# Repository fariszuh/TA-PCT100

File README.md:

# Tugas  Akhir PCT-100
Repository ini berisi file tugas akhir Implementasi PCT-100.
File yang tersedia berisi file program TA yang dibuat Penulis Muhammad Faris Zuhairi (2019 / Wisudawan 128 ITS), 
dengan judul berikut:

PERANCANGAN KONTROLER TERTANAM MENGGUNAKAN DIRECT NEURAL NETWORK UNTUK PENGATURAN LEVEL TANGKI PCT-100

Link Tugas Akhir: https://repository.its.ac.id/98936/ 
atau pada direktori "**Faris's Undergraduate Thesis (Buku TA)/07111940000164-Undergraduate_Thesis.pdf**"

Berikut foto prototype yang dibuat dan dihibahkan ke Lab. Kontrol dan Otomasi Dept. Teknik Elektro ITS

## 1. Tahap Permodelan
Tahap ini model plant diambil menggunakan identifikasi plant dan penurunan rumus. 
Permodelan dimulai dengan mengambil data menggunakan STM32 dengan hasil datasets terdapat pada folder berikut:
+ **/Datasets for Modelling & Test Result/**
  - **/Karakteristik Drain Valve/** :
  Data yang digunakan untuk memodelkan drain valve.

    Divariasikan: tegangan drain (Vdrain) dan tegangan flow control valve (Vfc).
    Dijaga konstan: tegangan pompa (Vpompa) 10V.

  - **/Karakteristik Flow Control Valve/** :
  Data yang digunakan untuk memodelkan flow control valve.

    Divariasikan: tegangan pompa (Vpompa) dan tegangan flow control valve (Vfc).
    Dijaga konstan: tegangan drain (Vdrain) tertutup (0 VDC).

  - **/Karakteristik Pompa/** :
  Data yang digunakan untuk memodelkan pompa inlet.

    Divariasikan: tegangan pompa (Vpompa).
    Dijaga konstan: tegangan drain (Vdrain) tertutup (0 VDC) dan dan tegangan flow control valve (22 VDC).

  - **/Karakteristik AI USB4716/** :
    Hasil pengujian DAC Amplifier AO STM32 dengan AI USB4716.
    Pengambilan data ini tanpa menghubungkan prototype ke plant (actuator dan sensor).
    Kode pengujian ini ada di folder **/Pengujian (Testing)/**.
  
    Divariasikan: tegangan AO STM32.

  - **/Karakteristik AO USB4716/** :
    Hasil pengujian ADC AI STM32 dengan AO USB4716.
    Pengambilan data ini tanpa menghubungkan prototype ke plant (actuator dan sensor).
    Kode pengujian ini ada di folder **/Pengujian (Testing)/**.

    Divariasikan: tegangan AO USB4716.

  - **/Pengujian NN/Implementasi/** :
    Hasil pengujian algoritma NN yang ditanam pada STM32.
    Pengambilan data ini dengan menghubungkan prototype ke plant (actuator dan sensor).
  
    Divariasikan: learning rate konstan dan nilai alpha (adaptasi learning rate) --> sudah dipisahkan dalam 2 folder yang berbeda.

  - **/Rafif Firdiansyah's Level Sensor Data/** :
    Excel workbook pembacaan tegangan level sensor dan simpangannya dengan level aktual (cm).

  - **/With Both Drain Valve/** :
    Data yang digunakan untuk memodelkan kedua valve pada kondisi berikut:
    Terbuka: manual dan motor drain valve.
    Tertutup: tidak ada.

      Divariasi: tegangan drain (Vdrain).
    
      Dijaga konstan: tegangan pompa (10 Vpompa) dan tegangan flow control valve (15 Vfc).
  
  - **/with Manual Valve/** :
    Data yang digunakan untuk memodelkan manual valve pada kondisi berikut:
    Terbuka: manual drain valve.
    Tertutup: motor drain valve --> tegangan drain (0 Vdrain) .

      Divariasi: tegangan pompa (Vpompa), dan tegangan flow control valve (Vfc).
    
      Dijaga konstan: full open manual valve.

  - **/with Proportional Drain Valve/** :
    Data yang digunakan untuk memodelkan motor valve pada kondisi berikut:
    Terbuka: motor drain valve.
    Tertutup: manual drain valve.

      Divariasi: tegangan flow control valve (15 Vfc).
    
      Dijaga konstan: tegangan drain (Vdrain) dan tegangan pompa (Vpompa).

Sedangkan, folder berikut berisi file program DAQ untuk pengambilan data plant.

+ **/MATLAB USB-4716/** : pengambilan data melalui DAQ Advantech USB-4716
  - **/Code TA Dedy Motor Induksi & Altivar 610/** : 
  Kode dan Tugas Akhir Dedy / Bambang Permadi Widyasmara tentang Kontrol PID-GA Motor Induksi.
    - Call.m : file utama yang hanya di run untuk mulai mengambil dan mengirim data.
    - ReadWrite.m : file library yang dibuatkan Faris (tidak perlu diubah-ubah).
    
  - **/Code USB4716 TA Faris (Worked)/** :
  File yang sudah diuji dan berhasil membaca AI dan mengirim AO.
    - **/Hasil Pengujian ADC-DAC STM32 dengan USB4716/** :
    Berisi file .mat workspace MATLAB pembacaan pengujian sinyal ramp AI dan AO dari Kit STM32 Implementasi.
    - CascadeController.m : mencoba menyusun kontroler cascade berdasarkan AI-AO
    - InstantAI.m : library default MATLAB untuk analog input DAQ
    - NN.m : mencoba menyusun kontroler Direct NN
    - Static_AO.m : library default MATLAB untuk analog output DAQ
    - Static_AO_custom.m : perubahan Static_AO.m agar bisa mengirim sinyal berubah2 (tidak terbatas default sawtooth, sine, square, dll)
    - Static_AO_simple.m : simplifikasi dari Static_AO_custom.m
  - **/Library Example Bawaan Navigator App/** :
  Library MATLAB yang didapatkan dari tutorial aplikasi Navigator.exe.
  - **/Library python-advantech-DAQNavi-bdaqctrl/** : 
  Library python untuk USB-4716, masih perlu compiler dari C ke python

+ /regresi : regresi respon level dan flow untuk mendapat gain scaling transmitter
  - regresi_FT.m : mencari gain flow meter untuk mengubah tegangan volt ke debit liter/menit (lt/min)
  - regresi_LT.m : mencari gain level sensor untuk mengubah tegangan volt ke level (mm)
+ /write_csv : testing program python data logger
  - save_data_fopen.py : test buka data csv menggunakan fungsi fopen()
  - save_data_withopen.py : test buka data csv menggunakan fungsi withopen()

## 2. Tahap Simulasi
Model yang telah diperoleh pada tahap sebelumnya digunakan untuk desain kontroler. 

+ **/Modelling & PCT-100 Simulation Testing/** :
  - **/MAT simulasi/** : 
  Berisi file .mat workspace MATLAB. Setpoint/SP divariasikan 100mm dan dynamic naik turun.
  MOV divariasi bukaan mulai 0%, 50% (aka 0.5), 100% (aka 1), dan dynamic (uniform random).
  Untuk Learning Rate (lr) konstan, alpha=0 dan lrinit divariasi mulai dari 1e-5 hingga 5.
  Namun, untuk Adaptasi Learning Rate melalui parameter alpha, divariasikan alpha mulai 1e-4 hingga 0.1, dimana alpha identik dengan kecepatan perubahan learning rate (lr).
  
  - **/Proteus DAC PWM/** :
  Berisi simulasi proteus untuk rangkaian PWM generator, amplifier teganan AO, dan filter sebelum diimplementasikan bersama STM32.
  
  - **/Tank Level Modelling/** :
  Simulasi kontroler berdasarkan model. Namun file terbarunya berada diluar folder ini (upper directory sekali).
  - closedLoop.slx : Simulink closed loop system
  - loadDatasets.m : file function matlab untuk membuka datasets untuk permodelan/menampilkan grafik respon
  - modellingDatasets.m : pengolahan raw data plant untuk mendapatkan gain scaling model
  - openLoop.slx : Simulasi open loop system

+ **/Pengujian (Testing)/** : Berisi kode untuk pengujian performa kontroller.
  - pengujian_ADC_AI_STM.m : pengujian ADC AI STM32 dengan menginjeksi tegangan AO sinyal ramp naik turun pada USB4716.
  - pengujian_ADC_A0_STM.m : pengujian DAC A0 STM32 dengan DAC STM32 menginjeksi tegangan sinyal ramp naik turun ke USB4716.
  - pengujian_lr.m : berisi kode untuk plot hasil model NN satu satu dari datasets.

## 3. Tahap Implementasi

+ **/Datasheet and Manual Embedded System Kit/** :
  Berisi datasheet dan manual komponen prototype Embedded System Kit.
  - **/ADAM 5000L-TCP/** : 
  Folder berisi Advantech ADAM5000L TCP installer, modbus simulator, dan RD9700 USB-Ethernet Driver
  
  - **/Manual Advantech USB4716/** :
  Folder berisi datasheet Advantech USB4716 dan Tugas Akhir yang menggunakan perangkat DAQ ini.
  Installer DAQ ini dapat didownload terbaru pada laman resmi Advantech, aplikasi utility dan drivernya ialah Navigator.exe.

  - **/Manual PCT100 by Bytronic/** :
  Folder berisi datasheet PCT-100 dan Burkert Proportional Valve 2835D.

+ **/Embedded System Kit PCB & Acrylic Box/** :
Berisi file PCB dan 3D Akrilik.
  - **/3D Akrilik/** :
  Berisi file cetak akrilik dan gcode 3D print casing USB-TTL Converter. 
  - **/Schematic PCB/** :
  Berisi file PCB Eagle.

+ **/Faris's Undergraduate Thesis (Buku TA)/** :
Berisi dokumen Seminar Tugas Akhir (STA Himatektro ITS) dan Tugas Akhir Faris.

+ **/Konten Sidang (Thesis Defense) dan Proposal/** :
Berisi file proposal (dokumen dan PPT sidang sempro) dan PPT sidang TA.

+ **/Manual Book Embedded System Kit/** :
Berisi manual book dari prototype Embedded System Kit yang sudah dibuat.
Harap pengguna prototype dan asisten Lab. Kontrol dan Otomasi ITS mempelajari ini.

+ **/PCT100 with ADAM 5000L MQTT/** :
  Implementasi PCT100 untuk TA Khoiruz (PID-PSO) dan TA Rafif (fuzzy MQTT) menggunakan ADAM5000L/TCP.

  - **/Modelling & Testing/** : Pengujian kontroler fuzzy dan PID dituning PSO
    - **/Datasets/** : Hasil pengambilan data openloop untuk TA Khoiruz dan Rafif
    - **/multiple subscribe fuzzy/** : testing program MQTT subscribe untuk kontroler fuzzy
        * Close Loop Fuzzy Multiple Subscribe.py : subscribe untuk closed loop system
        * MQTTtestMultipleSubscribe.py : test data masuk MQTT
    - **/scaling_regresi_flow_meter/** : 
    mencari gain scaling flow, raw data dari software PCT100 (bukan DAQ) oleh Khoiruz untuk permodelan plant. 
    - closedLoop_fuzzy.py : kontroler closed loop fuzzy
    - closedLoop_fuzzy_azzam.py : kontroler close loop fuzzy dengan rule base TA Hamzah Nur Azzam Motor Induksi
    - closedLoop_level.py : kontroler PID close loop level khoiruz
    - closedLoop_level_buTri.py : kontroler PID khoiruz hasil revisi penguji Bu Trihastuti
    - openLoop_level_flow.py : open loop untuk mendapat respon level dan flow identifikasi
    - readStreamModbus.py : Reverse engineering informasi stream Modbus UDP dari DAQ ADAM4000L/TCP
    - systemIdentification.py : Identifikasi sistem orde 1 + time delay dan orde 2 sesuai jurnal Jacoubek_Pavel
    - testRampMotorDC_SPA.py : pengujian sinyal kontrol ramp motor DC untuk tugas sistem pengaturan adaptif
    - testTs.py : pengujian untuk memperkecil timesampling Ts Modbus UDP DAQ ADAM4000L
    - testUDPmasAdrian.py : ambil data informasi AI UDP
    - testUDPmodbus2.py : ambil data informasi AI UDP dengan algoritma lain
  - **/Python GUI/** : Test coba desain GUI Python Modbus TCP
  - **/Regresi Sensor/** : berisi regresi level transmitter (LT) dan flow meter (FT).
  - **/Serial STM32/Send Command.py** : berisi kode untuk send command SP, Kp, Ki, Kd ke mikrokontroller STM32 sebagai parameter kontroller.
  - **/List Pin IO ADAM.xlsx** : List pin Input Output ADAM5000L dan berisi address register Modbus TCP.

+ **/Rafif's MQTT Mobile App/** : Settingan MQTT Rafif untuk kontroler fuzzy.
  - **/Konfigurasi APP IoT MQTT Panel/** : Konfigurasi IoT MQTT Panel (Aplikasi PlayStore).
  - testMQTT.py : implementasi python dengan app IoT MQTT Panel (playstore)

+ **/Receipt & Buying Report/** : Kumpulan nota dan laporan keuangan pembuatan prototype Embedded System Kit.
  Budget Rp1juta dari Lab. via Pak Eka Iskandar.
  - Rekap Nota Embedded System Kit_Update 19 Nov 2023.xlsx : Laporan keuangan masuk keluar dan total.

+ **/References for Citation/** : Kumpulan buku dan jurnal penelitian.
  - **/Faris's Journal Reference/** : 
  Referensi jurnal faris untuk neural network dan plant mathematical modelling.
  - **/PID ANFIS Hakhi** : 
  Referensi jurnal Hakhi berkaitan dengan ANFIS.
  - **/Previous Thesis/** : 
  Tugas akhir sebelumnya yang membahas coupled tank, PCT single tank, quadruple tank, NN, dan TA lain yang berkaitan.
  - **/System Identification Journal/** :
  Jurnal referensi identifikasi model system.
  - **/Theory Book/** :
  Buku teori yang dapat digunakan untuk dasar teori bab 2.

+ **/STM32/MultichannelADC/** : Pengujian kontroler dengan program yang sudah tertanam

## Documentation
+ **/Work Documentation/** : 
  berisi dokumentasi pekerjaan dengan Sobat PCT 2023.
### Faris's NN Implementation Video (showed during Final Project Presentation/Sidang TA)
1. PCT100 with constant Set Point https://www.youtube.com/watch?v=iwgPA4LB7lY&ab_channel=MuhammadFarisZuhairi
2. PCT100 with Increasing-Decreasing Set Point (step 50mm) https://www.youtube.com/watch?v=AL7DxppEuDM&ab_channel=MuhammadFarisZuhairi

### Team's Documentation
1. [28/03/2023 - Part 1 Paparan Progress Bimbingan TA PCT-100 at 23:24:33] https://youtu.be/hUXw9mhMRqU
2. [28/03/2023 - Part 2 Paparan Progress Bimbingan TA PCT-100 at 23:34:30] https://youtube.com/shorts/yUkm82Lsc_I
3. [28/03/2023 - Part 3 Paparan Progress Bimbingan TA PCT-100 at 23:35:58] https://youtu.be/i6Gw3u0Zylg
4. [28/03/2023 - Part 4 Paparan Progress Bimbingan TA PCT-100 at 23:44:26] https://youtu.be/1I7eSQTP36s
5. [29/03/2023 - Part 5 Paparan Progress Bimbingan TA PCT-100 at 23:04:08] https://youtu.be/HnbYzEy3LrQ

### Disclaimer
Apabila terdapat kebingungan pada program/struktur repository, silahkan menghubungi author IDLINE: fariszuh

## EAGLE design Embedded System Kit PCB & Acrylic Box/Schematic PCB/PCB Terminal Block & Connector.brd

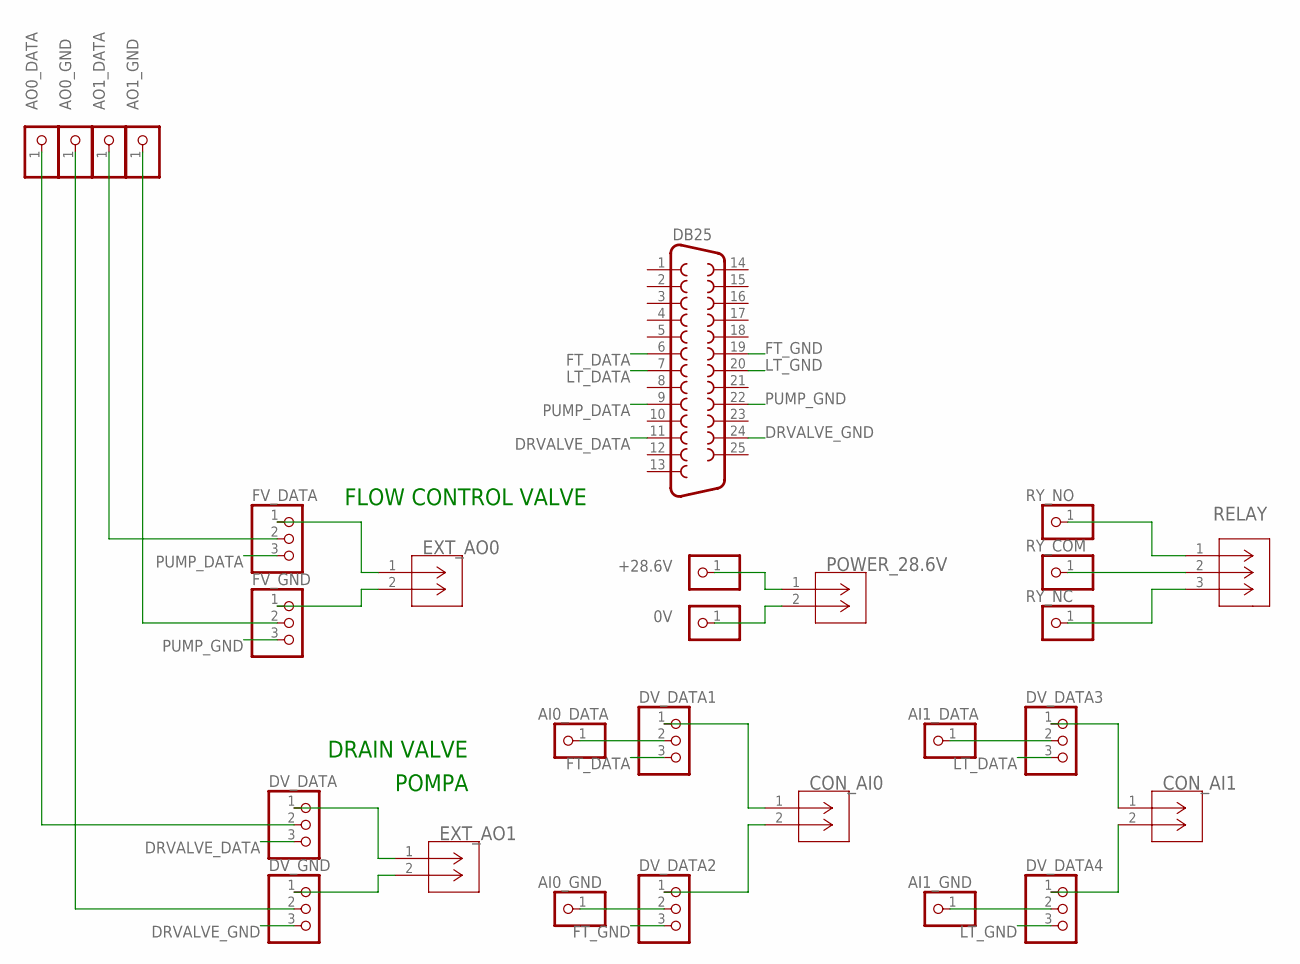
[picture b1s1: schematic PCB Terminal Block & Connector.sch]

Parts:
0V: PINHD-1X1; 1X01
+28.6V: PINHD-1X1; 1X01
AI0_DATA, AI0_GND, AI1_DATA, AI1_GND: PINHD-1X1; 1X01
AO0_DATA, AO0_GND, AO1_DATA, AO1_GND: PINHD-1X1; 1X01
CON_AI0, CON_AI1: KF8500-8.5-2P; CONN_KF8500-8.5-2P_CKE
DB25: F25H
DV_DATA, DV_DATA1, DV_DATA2, DV_DATA3, DV_DATA4: PINHD-1X3; 1X03
DV_GND: PINHD-1X3; 1X03
EXT_AO0, EXT_AO1: KF8500-8.5-2P; CONN_KF8500-8.5-2P_CKE
FV_DATA: PINHD-1X3; 1X03
FV_GND: PINHD-1X3; 1X03
POWER_28.6V: KF8500-8.5-2P; CONN_KF8500-8.5-2P_CKE
RELAY: KF8500-8.5-4P; CONN4_KF8500_1X4_1398X472_CKE
RY_COM: PINHD-1X1; 1X01
RY_NC: PINHD-1X1; 1X01
RY_NO: PINHD-1X1; 1X01

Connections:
AO0_DATA: AO0_DATA.1, DV_DATA.2
AO0_GND: AO0_GND.1, DV_GND.2
AO1_DATA: AO1_DATA.1, FV_DATA.2
AO1_GND: AO1_GND.1, FV_GND.2
DRVALVE_DATA: DB25.11, DV_DATA.3
DRVALVE_GND: DB25.24, DV_GND.3
EXT_AO2: DV_DATA.1, EXT_AO1.1
FT_DATA: DB25.6, DV_DATA1.3
FT_GND: DB25.19, DV_DATA2.3
LT_DATA: DB25.7, DV_DATA3.3
LT_GND: DB25.20, DV_DATA4.3
unnamed: +28.6V.1, POWER_28.6V.1
unnamed: 0V.1, POWER_28.6V.2
unnamed: EXT_AO0.2, FV_GND.1
unnamed: CON_AI0.1, DV_DATA1.1
unnamed: CON_AI1.1, DV_DATA3.1
unnamed: AI0_DATA.1, DV_DATA1.2
unnamed: AI0_GND.1, DV_DATA2.2
unnamed: CON_AI0.2, DV_DATA2.1
unnamed: EXT_AO0.1, FV_DATA.1
unnamed: CON_AI1.2, DV_DATA4.1
unnamed: AI1_DATA.1, DV_DATA3.2
unnamed: DV_GND.1, EXT_AO1.2
unnamed: RELAY.2, RY_COM.1
unnamed: AI1_GND.1, DV_DATA4.2
unnamed: RELAY.3, RY_NC.1
unnamed: RELAY.1, RY_NO.1
PUMP_DATA: DB25.9, FV_DATA.3
PUMP_GND: DB25.22, FV_GND.3

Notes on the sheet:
FLOW CONTROL VALVE
DRAIN VALVE
POMPA

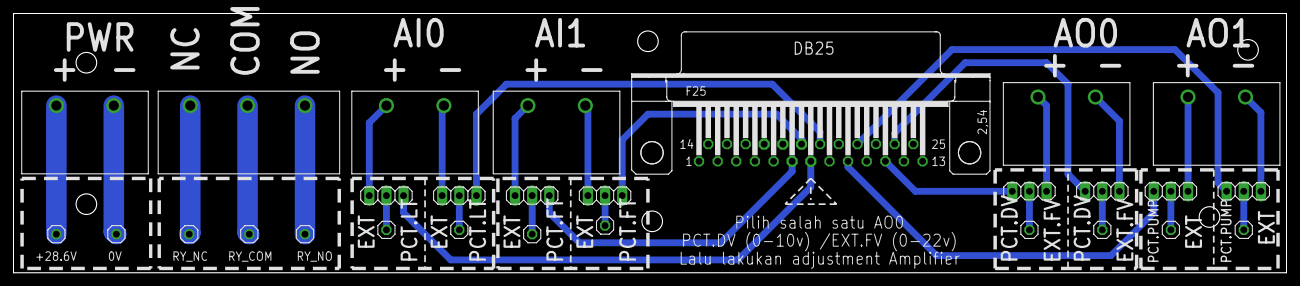
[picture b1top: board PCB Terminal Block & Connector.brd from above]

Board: 2 copper layers, 188.6 x 38.4 mm, 28 parts (0 on the bottom side), 29 nets.

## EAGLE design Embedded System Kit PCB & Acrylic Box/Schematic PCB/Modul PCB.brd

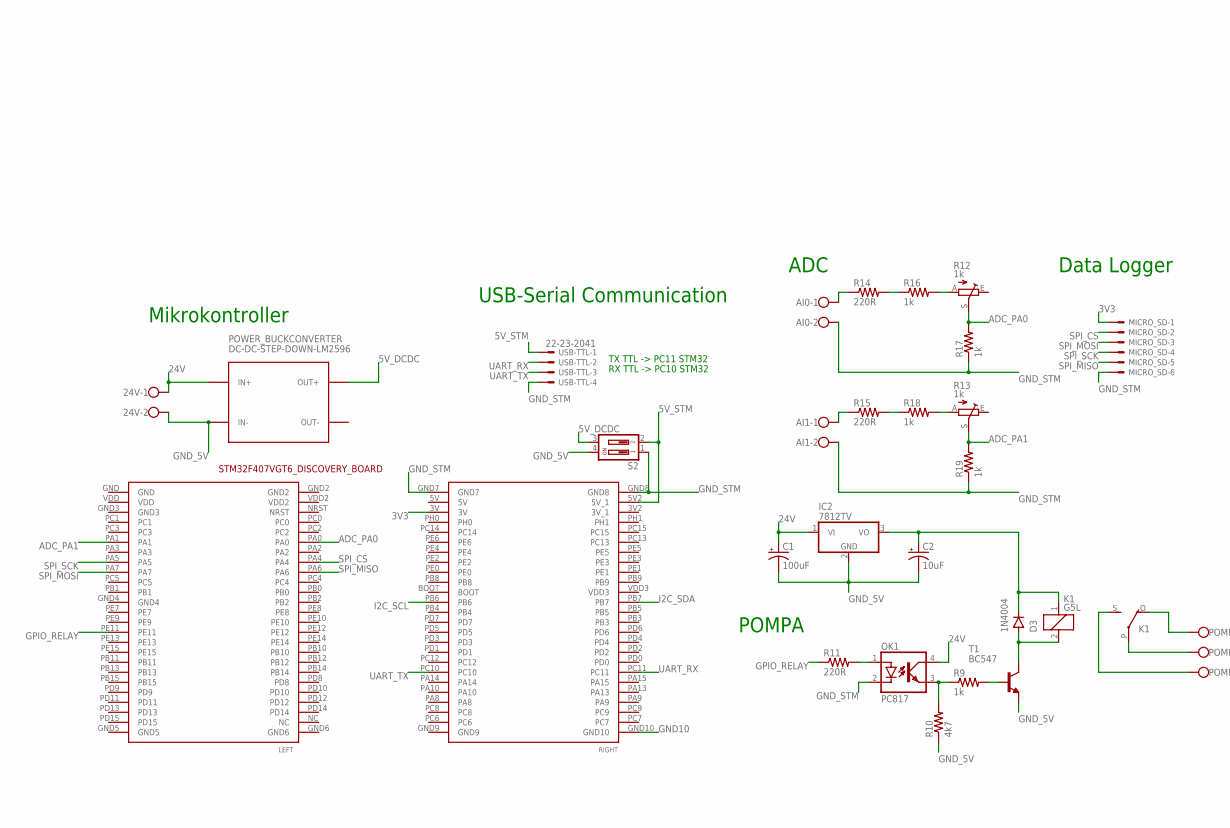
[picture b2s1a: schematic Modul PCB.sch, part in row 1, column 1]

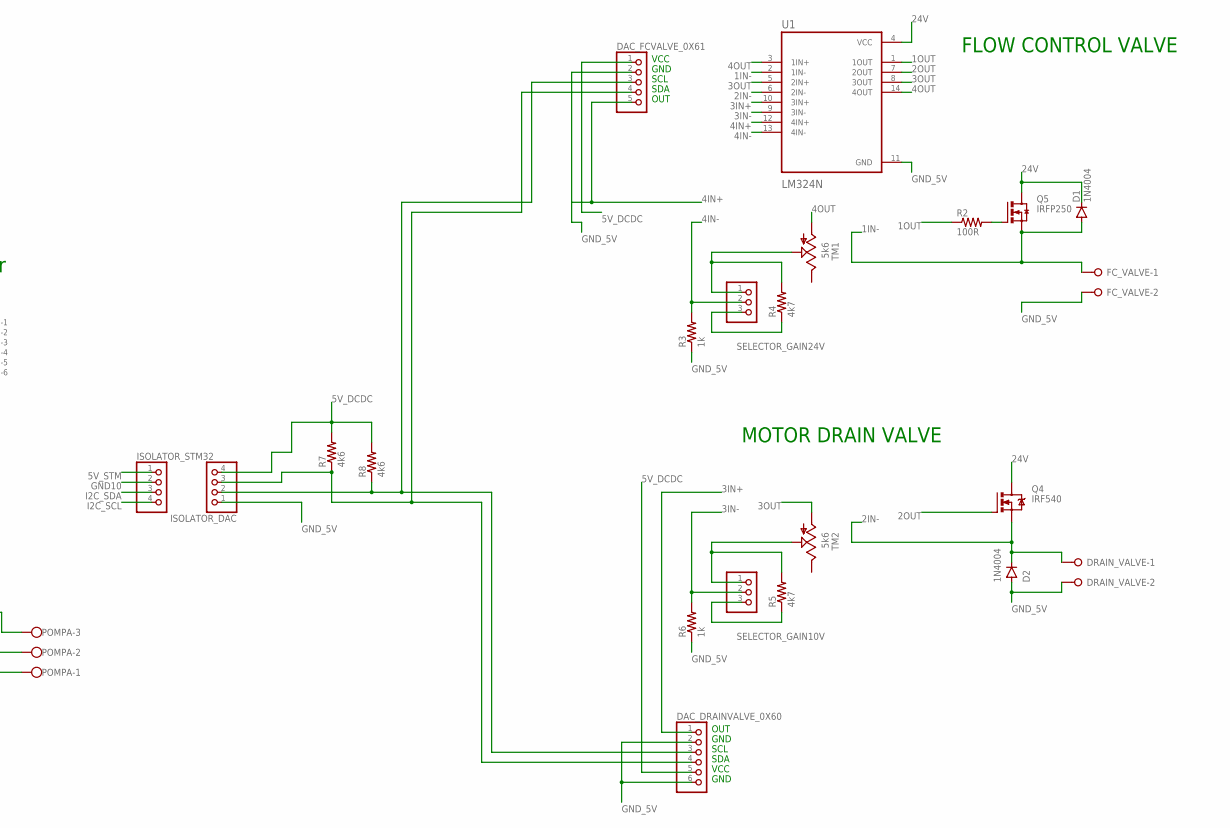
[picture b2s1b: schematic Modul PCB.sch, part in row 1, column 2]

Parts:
24V: W237-102
AI0, AI1: W237-102
C1: 100uF; E2,5-6
C2: 10uF; E2,5-6
D1, D2, D3: 1N4004; DO41-10
DAC_DRAINVALVE_0X60: PINHD-1X6; 1X06
DAC_FCVALVE_0X61: PINHD-1X5; 1X05
DRAIN_VALVE: W237-02P; W237-132
FC_VALVE: W237-02P; W237-132
IC2: 7812TV; TO220V
ISOLATOR_DAC: PINHD-1X4; 1X04
ISOLATOR_STM32: PINHD-1X4; 1X04
K1: G5L; G5LE
MICRO_SD: 22-23-2061
OK1: PC817; DIL04
POMPA: W237-103
POWER_BUCKCONVERTER: DC-DC-STEP-DOWN-LM2596
Q4: IRF540; TO220BV
Q5: IRFP250; TO-247AD-V
R2: 100R; 0207/10
R3, R6, R9, R16, R17, R18, R19: 1k; 0207/10
R4, R5, R10: 4k7; 0207/10
R7, R8: 4k6; 0207/10
R11, R14, R15: 220R; 0207/10
R12, R13: 1k; RJ9W
S2: DS02; DS-02
SELECTOR_GAIN10V, SELECTOR_GAIN24V: PINHD-1X3; 1X03
STM32F407VGT6_DISCOVERY_BOARD: STM32F4-DISCOVERY; STM32F407VG
T1: BC547; TO92
TM1, TM2: 5k6; 6MM
U1: LM324N; DIP794W45P254L1969H508Q14
USB-TTL: 22-23-2041

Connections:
1IN-: D1.A, FC_VALVE.1, Q5.S, U1.2 (1IN-)
1OUT: R2.1, U1.1 (1OUT)
2IN-: D2.C, DRAIN_VALVE.1, Q4.S, U1.6 (2IN-)
2OUT: Q4.G, U1.7 (2OUT)
3IN+: DAC_DRAINVALVE_0X60.1, U1.10 (3IN+)
3IN-: R6.2, SELECTOR_GAIN10V.2, U1.9 (3IN-)
3OUT: TM2.A, U1.5 (2IN+), U1.8 (3OUT)
3V3: MICRO_SD.1, STM32F407VGT6_DISCOVERY_BOARD.3V
4IN+: DAC_FCVALVE_0X61.5, U1.12 (4IN+)
4IN-: R3.2, SELECTOR_GAIN24V.2, U1.13 (4IN-)
4OUT: TM1.A, U1.3 (1IN+), U1.14 (4OUT)
5V_DCDC: DAC_DRAINVALVE_0X60.5, DAC_FCVALVE_0X61.1, ISOLATOR_DAC.4, POWER_BUCKCONVERTER.OUT+, R7.2, R8.2, S2.3
5V_STM: ISOLATOR_STM32.1, S2.2, STM32F407VGT6_DISCOVERY_BOARD.5V2 (5V_1), USB-TTL.1
24V: 24V.1, C1.+, D1.C, IC2.1 (VI), OK1.4 (COL), POWER_BUCKCONVERTER.IN+, Q4.D, Q5.D, U1.4 (VCC)
ADC_PA0: R12.S, R17.2, STM32F407VGT6_DISCOVERY_BOARD.PA0
ADC_PA1: R13.S, R19.2, STM32F407VGT6_DISCOVERY_BOARD.PA1
GND10: ISOLATOR_STM32.2, STM32F407VGT6_DISCOVERY_BOARD.GND10
GND_5V: 24V.2, C1.-, C2.-, D2.A, DAC_DRAINVALVE_0X60.2, DAC_DRAINVALVE_0X60.6, DAC_FCVALVE_0X61.2, DRAIN_VALVE.2, FC_VALVE.2, IC2.2 (GND), ISOLATOR_DAC.1, POWER_BUCKCONVERTER.IN-, R3.1, R6.1, R10.1, S2.4, T1.1 (E), U1.11 (GND)
GND_STM: AI0.2, AI1.2, MICRO_SD.6, OK1.2 (C), R17.1, R19.1, S2.1, STM32F407VGT6_DISCOVERY_BOARD.GND7, STM32F407VGT6_DISCOVERY_BOARD.GND8, USB-TTL.4
GPIO_RELAY: R11.1, STM32F407VGT6_DISCOVERY_BOARD.PE11
I2C_SCL: ISOLATOR_STM32.4, STM32F407VGT6_DISCOVERY_BOARD.PB6
I2C_SDA: ISOLATOR_STM32.3, STM32F407VGT6_DISCOVERY_BOARD.PB7
unnamed: Q5.G, R2.2
unnamed: R4.1, SELECTOR_GAIN24V.3
unnamed: R4.2, SELECTOR_GAIN24V.1, TM1.S
unnamed: R5.2, SELECTOR_GAIN10V.1, TM2.S
unnamed: R5.1, SELECTOR_GAIN10V.3
unnamed: R9.2, T1.2 (B)
unnamed: DAC_DRAINVALVE_0X60.4, DAC_FCVALVE_0X61.4, ISOLATOR_DAC.3, R7.1
unnamed: DAC_DRAINVALVE_0X60.3, DAC_FCVALVE_0X61.3, ISOLATOR_DAC.2, R8.1
unnamed: D3.A, K1.2, T1.3 (C)
unnamed: OK1.3 (EMIT), R9.1, R10.2
unnamed: K1.P, POMPA.2
unnamed: K1.S, POMPA.1
unnamed: K1.O, POMPA.3
unnamed: OK1.1 (A), R11.2
unnamed: AI0.1, R14.1
unnamed: R14.2, R16.1
unnamed: R12.A, R16.2
unnamed: AI1.1, R15.1
unnamed: R15.2, R18.1
unnamed: R13.A, R18.2
unnamed: C2.+, D3.C, IC2.3 (VO), K1.1
SPI_CS: MICRO_SD.2, STM32F407VGT6_DISCOVERY_BOARD.PA4
SPI_MISO: MICRO_SD.5, STM32F407VGT6_DISCOVERY_BOARD.PA6
SPI_MOSI: MICRO_SD.3, STM32F407VGT6_DISCOVERY_BOARD.PA7
SPI_SCK: MICRO_SD.4, STM32F407VGT6_DISCOVERY_BOARD.PA5
UART_RX: STM32F407VGT6_DISCOVERY_BOARD.PC11, USB-TTL.2
UART_TX: STM32F407VGT6_DISCOVERY_BOARD.PC10, USB-TTL.3

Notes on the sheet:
FLOW CONTROL VALVE
MOTOR DRAIN VALVE
POMPA
ADC
TX TTL -> PC11 STM32
RX TTL -> PC10 STM32
USB-Serial Communication
Data Logger
Mikrokontroller
OUT
GND
SCL
SDA
VCC

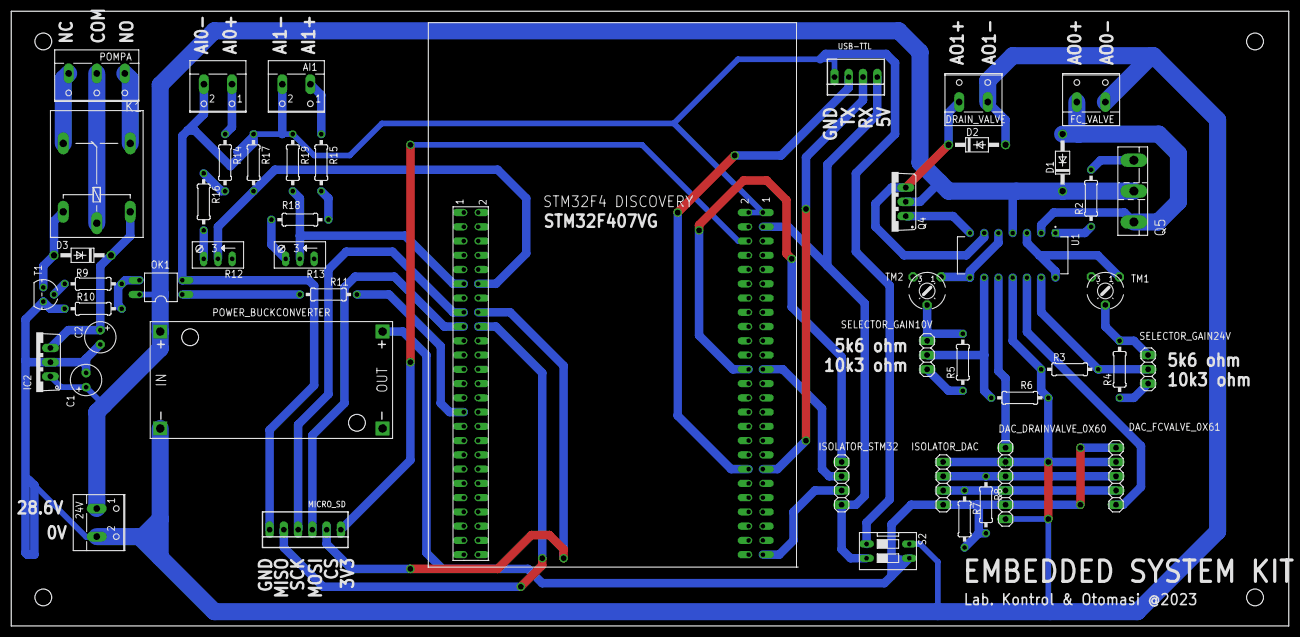
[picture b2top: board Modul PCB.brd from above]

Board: 2 copper layers, 227.6 x 109.5 mm, 49 parts (0 on the bottom side), 49 nets.

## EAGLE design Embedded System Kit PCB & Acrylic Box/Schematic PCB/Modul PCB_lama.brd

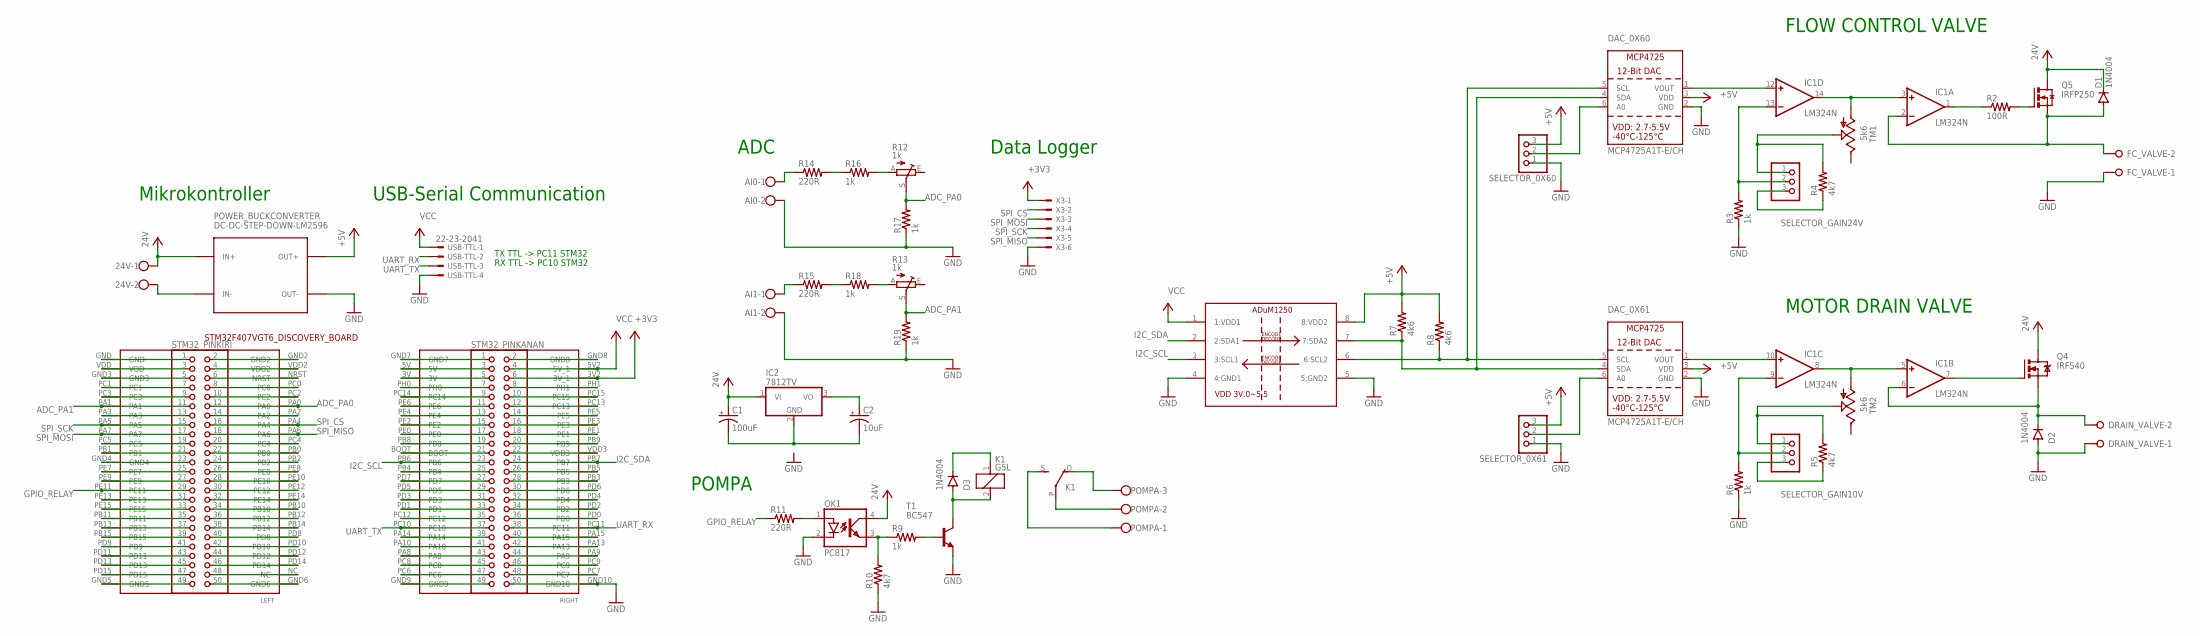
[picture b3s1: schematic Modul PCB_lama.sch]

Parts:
24V: W237-102
AI0, AI1: W237-102
C1: 100uF; E2,5-6
C2: 10uF; E2,5-6
D1, D2, D3: 1N4004; DO41-10
DAC_0X60, DAC_0X61: MCP4725A1T-E/CH; SOT23-6
DRAIN_VALVE: W237-02P; W237-132
FC_VALVE: W237-02P; W237-132
IC1: LM324N; DIL14
IC2: 7812TV; TO220V
K1: G5L; G5LE
OK1: PC817; DIL04
POMPA: W237-103
POWER_BUCKCONVERTER: DC-DC-STEP-DOWN-LM2596
Q4: IRF540; TO220BV
Q5: IRFP250; TO-247AD-V
R2: 100R; 0207/10
R3, R6, R9, R16, R17, R18, R19: 1k; 0207/10
R4, R5, R10: 4k7; 0207/10
R7, R8: 4k6; 0207/10
R11, R14, R15: 220R; 0207/10
R12, R13: 1k; RJ9W
SELECTOR_0X60, SELECTOR_0X61: PINHD-1X3; 1X03
SELECTOR_GAIN10V, SELECTOR_GAIN24V: PINHD-1X3; 1X03
STM32F407VGT6_DISCOVERY_BOARD: STM32F4-DISCOVERY; STM32F407VG
STM32_PINKANAN, STM32_PINKIRI: PINHD-2X25; 2X25
T1: BC547; TO92
TM1, TM2: 5k6; 6MM
U$1: ADUM1250; SOIC_N
USB-TTL: 22-23-2041
X3: 22-23-2061

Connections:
+3V3: STM32F407VGT6_DISCOVERY_BOARD.3V2 (3V_1), STM32_PINKANAN.6, X3.1
+5V: DAC_0X60.3 (VDD), DAC_0X61.3 (VDD), POWER_BUCKCONVERTER.OUT+, R7.2, R8.2, SELECTOR_0X60.3, SELECTOR_0X61.3, U$1.8 (8:VDD2)
ADC_PA0: R12.S, R17.2, STM32F407VGT6_DISCOVERY_BOARD.PA0, STM32_PINKIRI.12
ADC_PA1: R13.S, R19.2, STM32F407VGT6_DISCOVERY_BOARD.PA1, STM32_PINKIRI.11
GND: AI0.2, AI1.2, D2.A, DAC_0X60.2 (GND), DAC_0X61.2 (GND), DRAIN_VALVE.1, FC_VALVE.1, OK1.2 (C), POWER_BUCKCONVERTER.OUT-, R3.1, R6.1, R10.1, R17.1, R19.1, SELECTOR_0X60.1, SELECTOR_0X61.1, STM32F407VGT6_DISCOVERY_BOARD.GND10, STM32_PINKANAN.50, T1.1 (E), U$1.4 (4:GND1), U$1.5 (5:GND2), USB-TTL.4, X3.6
GPIO_RELAY: R11.1, STM32F407VGT6_DISCOVERY_BOARD.PE11, STM32_PINKIRI.29
I2C_SCL: STM32F407VGT6_DISCOVERY_BOARD.PB6, STM32_PINKANAN.23, U$1.3 (3:SCL1)
I2C_SDA: STM32F407VGT6_DISCOVERY_BOARD.PB7, STM32_PINKANAN.24, U$1.2 (2:SDA1)
unnamed: IC1.1 (OUT), R2.1
unnamed: D2.C, DRAIN_VALVE.2, IC1.6 (-IN), Q4.S
unnamed: IC1.7 (OUT), Q4.G
unnamed: Q5.G, R2.2
unnamed: IC1.3 (+IN), IC1.14 (OUT), TM1.A
unnamed: IC1.5 (+IN), IC1.8 (OUT), TM2.A
unnamed: D1.A, FC_VALVE.2, IC1.2 (-IN), Q5.S
unnamed: IC1.13 (-IN), R3.2, SELECTOR_GAIN24V.2
unnamed: R4.1, SELECTOR_GAIN24V.3
unnamed: R4.2, SELECTOR_GAIN24V.1, TM1.S
unnamed: R5.2, SELECTOR_GAIN10V.1, TM2.S
unnamed: IC1.9 (-IN), R6.2, SELECTOR_GAIN10V.2
unnamed: R5.1, SELECTOR_GAIN10V.3
unnamed: DAC_0X60.1 (VOUT), IC1.12 (+IN)
unnamed: DAC_0X61.1 (VOUT), IC1.10 (+IN)
unnamed: R9.2, T1.2 (B)
unnamed: 24V.2, POWER_BUCKCONVERTER.IN-
unnamed: DAC_0X60.6 (A0), SELECTOR_0X60.2
unnamed: DAC_0X60.4 (SDA), DAC_0X61.4 (SDA), R7.1, U$1.7 (7:SDA2)
unnamed: DAC_0X60.5 (SCL), DAC_0X61.5 (SCL), R8.1, U$1.6 (6:SCL2)
unnamed: D3.A, K1.2, T1.3 (C)
unnamed: DAC_0X61.6 (A0), SELECTOR_0X61.2
unnamed: OK1.3 (EMIT), R9.1, R10.2
unnamed: K1.P, POMPA.2
unnamed: K1.S, POMPA.1
unnamed: K1.O, POMPA.3
unnamed: OK1.1 (A), R11.2
unnamed: AI0.1, R14.1
unnamed: R14.2, R16.1
unnamed: R12.A, R16.2
unnamed: D3.C, K1.1
unnamed: AI1.1, R15.1
unnamed: STM32F407VGT6_DISCOVERY_BOARD.GND, STM32_PINKIRI.1
unnamed: R15.2, R18.1
unnamed: R13.A, R18.2
unnamed: C2.+, IC2.3 (VO)
unnamed: C1.-, C2.-, IC2.2 (GND)
unnamed: STM32F407VGT6_DISCOVERY_BOARD.VDD, STM32_PINKIRI.3
unnamed: STM32F407VGT6_DISCOVERY_BOARD.GND3, STM32_PINKIRI.5
unnamed: STM32F407VGT6_DISCOVERY_BOARD.PC1, STM32_PINKIRI.7
unnamed: STM32F407VGT6_DISCOVERY_BOARD.PC3, STM32_PINKIRI.9
unnamed: STM32F407VGT6_DISCOVERY_BOARD.PA3, STM32_PINKIRI.13
unnamed: STM32F407VGT6_DISCOVERY_BOARD.PC5, STM32_PINKIRI.19
unnamed: STM32F407VGT6_DISCOVERY_BOARD.PB1, STM32_PINKIRI.21
unnamed: STM32F407VGT6_DISCOVERY_BOARD.GND4, STM32_PINKIRI.23
unnamed: STM32F407VGT6_DISCOVERY_BOARD.PE7, STM32_PINKIRI.25
unnamed: STM32F407VGT6_DISCOVERY_BOARD.PE9, STM32_PINKIRI.27
unnamed: STM32F407VGT6_DISCOVERY_BOARD.PE13, STM32_PINKIRI.31
unnamed: STM32F407VGT6_DISCOVERY_BOARD.PE15, STM32_PINKIRI.33
unnamed: STM32F407VGT6_DISCOVERY_BOARD.PB11, STM32_PINKIRI.35
unnamed: STM32F407VGT6_DISCOVERY_BOARD.PB13, STM32_PINKIRI.37
unnamed: STM32F407VGT6_DISCOVERY_BOARD.PB15, STM32_PINKIRI.39
unnamed: STM32F407VGT6_DISCOVERY_BOARD.PD9, STM32_PINKIRI.41
unnamed: STM32F407VGT6_DISCOVERY_BOARD.PD11, STM32_PINKIRI.43
unnamed: STM32F407VGT6_DISCOVERY_BOARD.PD13, STM32_PINKIRI.45
unnamed: STM32F407VGT6_DISCOVERY_BOARD.PD15, STM32_PINKIRI.47
unnamed: STM32F407VGT6_DISCOVERY_BOARD.GND5, STM32_PINKIRI.49
unnamed: STM32F407VGT6_DISCOVERY_BOARD.GND6, STM32_PINKIRI.50
unnamed: STM32F407VGT6_DISCOVERY_BOARD.NC, STM32_PINKIRI.48
unnamed: STM32F407VGT6_DISCOVERY_BOARD.PD14, STM32_PINKIRI.46
unnamed: STM32F407VGT6_DISCOVERY_BOARD.PD12, STM32_PINKIRI.44
unnamed: STM32F407VGT6_DISCOVERY_BOARD.PD10, STM32_PINKIRI.42
unnamed: STM32F407VGT6_DISCOVERY_BOARD.PD8, STM32_PINKIRI.40
unnamed: STM32F407VGT6_DISCOVERY_BOARD.PB14, STM32_PINKIRI.38
unnamed: STM32F407VGT6_DISCOVERY_BOARD.PB12, STM32_PINKIRI.36
unnamed: STM32F407VGT6_DISCOVERY_BOARD.PB10, STM32_PINKIRI.34
unnamed: STM32F407VGT6_DISCOVERY_BOARD.PE14, STM32_PINKIRI.32
unnamed: STM32F407VGT6_DISCOVERY_BOARD.PE12, STM32_PINKIRI.30
unnamed: STM32F407VGT6_DISCOVERY_BOARD.PE10, STM32_PINKIRI.28
unnamed: STM32F407VGT6_DISCOVERY_BOARD.PE8, STM32_PINKIRI.26
unnamed: STM32F407VGT6_DISCOVERY_BOARD.PB2, STM32_PINKIRI.24
unnamed: STM32F407VGT6_DISCOVERY_BOARD.PB0, STM32_PINKIRI.22
unnamed: STM32F407VGT6_DISCOVERY_BOARD.GND2, STM32_PINKIRI.2
unnamed: STM32F407VGT6_DISCOVERY_BOARD.VDD2, STM32_PINKIRI.4
unnamed: STM32F407VGT6_DISCOVERY_BOARD.NRST, STM32_PINKIRI.6
unnamed: STM32F407VGT6_DISCOVERY_BOARD.PC0, STM32_PINKIRI.8
unnamed: STM32F407VGT6_DISCOVERY_BOARD.PC2, STM32_PINKIRI.10
unnamed: STM32F407VGT6_DISCOVERY_BOARD.PA2, STM32_PINKIRI.14
unnamed: STM32F407VGT6_DISCOVERY_BOARD.PC4, STM32_PINKIRI.20
unnamed: STM32F407VGT6_DISCOVERY_BOARD.GND7, STM32_PINKANAN.1
unnamed: STM32F407VGT6_DISCOVERY_BOARD.5V, STM32_PINKANAN.3
unnamed: STM32F407VGT6_DISCOVERY_BOARD.3V, STM32_PINKANAN.5
unnamed: STM32F407VGT6_DISCOVERY_BOARD.PH0, STM32_PINKANAN.7
unnamed: STM32F407VGT6_DISCOVERY_BOARD.PC14, STM32_PINKANAN.9
unnamed: STM32F407VGT6_DISCOVERY_BOARD.PE6, STM32_PINKANAN.11
unnamed: STM32F407VGT6_DISCOVERY_BOARD.PE4, STM32_PINKANAN.13
unnamed: STM32F407VGT6_DISCOVERY_BOARD.PE2, STM32_PINKANAN.15
unnamed: STM32F407VGT6_DISCOVERY_BOARD.PE0, STM32_PINKANAN.17
unnamed: STM32F407VGT6_DISCOVERY_BOARD.PB8, STM32_PINKANAN.19
unnamed: STM32F407VGT6_DISCOVERY_BOARD.BOOT, STM32_PINKANAN.21
unnamed: STM32F407VGT6_DISCOVERY_BOARD.PB4, STM32_PINKANAN.25
unnamed: STM32F407VGT6_DISCOVERY_BOARD.PD7, STM32_PINKANAN.27
unnamed: STM32F407VGT6_DISCOVERY_BOARD.PD5, STM32_PINKANAN.29
unnamed: STM32F407VGT6_DISCOVERY_BOARD.PD3, STM32_PINKANAN.31
unnamed: STM32F407VGT6_DISCOVERY_BOARD.PD1, STM32_PINKANAN.33
unnamed: STM32F407VGT6_DISCOVERY_BOARD.PC12, STM32_PINKANAN.35
unnamed: STM32F407VGT6_DISCOVERY_BOARD.PA14, STM32_PINKANAN.39
unnamed: STM32F407VGT6_DISCOVERY_BOARD.PA10, STM32_PINKANAN.41
unnamed: STM32F407VGT6_DISCOVERY_BOARD.PA8, STM32_PINKANAN.43
unnamed: STM32F407VGT6_DISCOVERY_BOARD.PC8, STM32_PINKANAN.45
unnamed: STM32F407VGT6_DISCOVERY_BOARD.PC6, STM32_PINKANAN.47
unnamed: STM32F407VGT6_DISCOVERY_BOARD.GND9, STM32_PINKANAN.49
unnamed: STM32F407VGT6_DISCOVERY_BOARD.PC7, STM32_PINKANAN.48
unnamed: STM32F407VGT6_DISCOVERY_BOARD.PC9, STM32_PINKANAN.46
unnamed: STM32F407VGT6_DISCOVERY_BOARD.PA9, STM32_PINKANAN.44
unnamed: STM32F407VGT6_DISCOVERY_BOARD.PA13, STM32_PINKANAN.42
unnamed: STM32F407VGT6_DISCOVERY_BOARD.PA15, STM32_PINKANAN.40
unnamed: STM32F407VGT6_DISCOVERY_BOARD.PD0, STM32_PINKANAN.36
unnamed: STM32F407VGT6_DISCOVERY_BOARD.PD2, STM32_PINKANAN.34
unnamed: STM32F407VGT6_DISCOVERY_BOARD.PD4, STM32_PINKANAN.32
unnamed: STM32F407VGT6_DISCOVERY_BOARD.PD6, STM32_PINKANAN.30
unnamed: STM32F407VGT6_DISCOVERY_BOARD.PB3, STM32_PINKANAN.28
unnamed: STM32F407VGT6_DISCOVERY_BOARD.PB5, STM32_PINKANAN.26
unnamed: STM32F407VGT6_DISCOVERY_BOARD.VDD3, STM32_PINKANAN.22
unnamed: STM32F407VGT6_DISCOVERY_BOARD.PB9, STM32_PINKANAN.20
unnamed: STM32F407VGT6_DISCOVERY_BOARD.GND8, STM32_PINKANAN.2
unnamed: STM32F407VGT6_DISCOVERY_BOARD.PH1, STM32_PINKANAN.8
unnamed: STM32F407VGT6_DISCOVERY_BOARD.PC15, STM32_PINKANAN.10
unnamed: STM32F407VGT6_DISCOVERY_BOARD.PC13, STM32_PINKANAN.12
unnamed: STM32F407VGT6_DISCOVERY_BOARD.PE5, STM32_PINKANAN.14
unnamed: STM32F407VGT6_DISCOVERY_BOARD.PE3, STM32_PINKANAN.16
unnamed: STM32F407VGT6_DISCOVERY_BOARD.PE1, STM32_PINKANAN.18
SPI_CS: STM32F407VGT6_DISCOVERY_BOARD.PA4, STM32_PINKIRI.16, X3.2
SPI_MISO: STM32F407VGT6_DISCOVERY_BOARD.PA6, STM32_PINKIRI.18, X3.5
SPI_MOSI: STM32F407VGT6_DISCOVERY_BOARD.PA7, STM32_PINKIRI.17, X3.3
SPI_SCK: STM32F407VGT6_DISCOVERY_BOARD.PA5, STM32_PINKIRI.15, X3.4
UART_RX: STM32F407VGT6_DISCOVERY_BOARD.PC11, STM32_PINKANAN.38, USB-TTL.2
UART_TX: STM32F407VGT6_DISCOVERY_BOARD.PC10, STM32_PINKANAN.37, USB-TTL.3
V+: IC1.4 (V+)
V-: IC1.11 (V-)
VCC: 24V.1, C1.+, D1.C, IC2.1 (VI), OK1.4 (COL), POWER_BUCKCONVERTER.IN+, Q4.D, Q5.D, STM32F407VGT6_DISCOVERY_BOARD.5V2 (5V_1), STM32_PINKANAN.4, U$1.1 (1:VDD1), USB-TTL.1

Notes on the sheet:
FLOW CONTROL VALVE
MOTOR DRAIN VALVE
POMPA
ADC
TX TTL -> PC11 STM32
RX TTL -> PC10 STM32
USB-Serial Communication
Data Logger
Mikrokontroller

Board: 2 copper layers, 51 parts (0 on the bottom side), 137 nets, no tracks yet.

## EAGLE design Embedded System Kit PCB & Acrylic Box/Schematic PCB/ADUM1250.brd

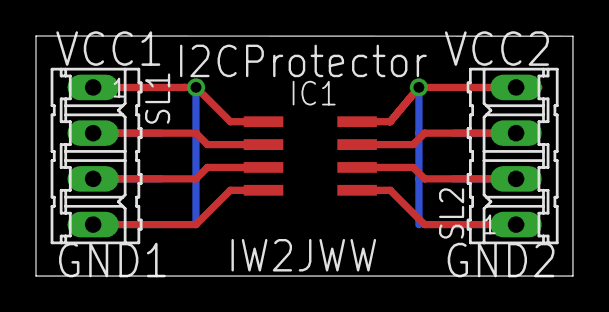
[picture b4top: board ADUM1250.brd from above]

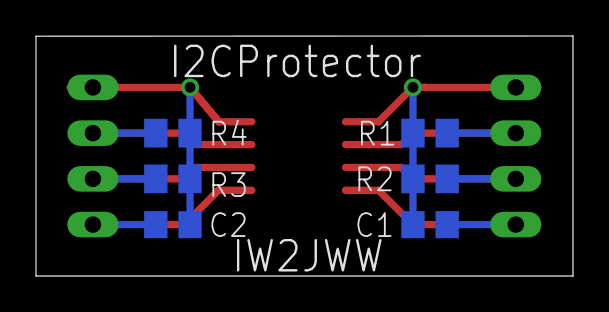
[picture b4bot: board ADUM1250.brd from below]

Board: 2 copper layers, 29.8 x 13.3 mm, 9 parts (6 on the bottom side), 8 nets.

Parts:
C1, C2: 100nF; C0805
IC1: ADUM1250; SO8
R1, R2, R3, R4: 3k3; M0805
SL1, SL2: 04P

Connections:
GND1: C1.1, IC1.4, SL1.4
GND2: C2.1, IC1.5, SL2.1
unnamed: IC1.2, R1.2, SL1.2
unnamed: IC1.3, R2.1, SL1.3
unnamed: IC1.6, R3.1, SL2.2
unnamed: IC1.7, R4.1, SL2.3
VDD1: C1.2, IC1.1, R1.1, R2.2, SL1.1
VDD2: C2.2, IC1.8, R3.2, R4.2, SL2.4

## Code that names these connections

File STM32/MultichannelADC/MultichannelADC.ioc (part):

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Mcu.Name=STM32F407V(E-G)Tx
Mcu.Package=LQFP100
Mcu.UserName=STM32F407VGTx
PA0-WKUP.Signal=ADCx_IN0
PA1.Signal=ADCx_IN1
PA13.Mode=Serial_Wire
PA13.Signal=SYS_JTMS-SWDIO
PA14.Mode=Serial_Wire
PA14.Signal=SYS_JTCK-SWCLK
PA2.Signal=ADCx_IN2
PA4.GPIOParameters=GPIO_PuPd
PA4.GPIO_PuPd=GPIO_PULLUP
PA4.Signal=GPIO_Output
PA5.GPIOParameters=GPIO_PuPd
PA5.GPIO_PuPd=GPIO_PULLUP
PA5.Mode=Full_Duplex_Master
PA5.Signal=SPI1_SCK
PA6.GPIOParameters=GPIO_PuPd
PA6.GPIO_PuPd=GPIO_PULLUP
PA6.Mode=Full_Duplex_Master
PA6.Signal=SPI1_MISO
PA7.GPIOParameters=GPIO_PuPd
PA7.GPIO_PuPd=GPIO_PULLUP
PA7.Mode=Full_Duplex_Master
PA7.Signal=SPI1_MOSI
PB10.GPIOParameters=GPIO_Pu
PB10.GPIO_Pu=GPIO_PULLUP
PB10.Mode=I2C
PB10.Signal=I2C2_SCL
PB11.GPIOParameters=GPIO_Pu
PB11.GPIO_Pu=GPIO_PULLUP
PB11.Mode=I2C
PB11.Signal=I2C2_SDA
PB6.GPIOParameters=GPIO_Pu
PB6.GPIO_Pu=GPIO_PULLUP
PB6.Mode=I2C
PB6.Signal=I2C1_SCL
PB7.GPIOParameters=GPIO_Pu
PB7.GPIO_Pu=GPIO_PULLUP
PB7.Mode=I2C
PB7.Signal=I2C1_SDA
PC10.Mode=Asynchronous
PC10.Signal=UART4_TX
PC11.Mode=Asynchronous
PC11.Signal=UART4_RX
PE11.Signal=GPIO_Output
PE9.Signal=S_TIM1_CH1
PH0-OSC_IN.Mode=HSE-External-Oscillator
PH0-OSC_IN.Signal=RCC_OSC_IN
PH1-OSC_OUT.Mode=HSE-External-Oscillator
PH1-OSC_OUT.Signal=RCC_OSC_OUT
RCC.HSE_VALUE=8000000
RCC.SYSCLKFreq_VALUE=168000000
RCC.SYSCLKSource=RCC_SYSCLKSOURCE_PLLCLK
board=custom

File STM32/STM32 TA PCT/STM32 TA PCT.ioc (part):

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Mcu.Name=STM32F407V(E-G)Tx
Mcu.Package=LQFP100
Mcu.UserName=STM32F407VGTx
PA10.Mode=Asynchronous
PA10.Signal=USART1_RX
PA13.Mode=Serial_Wire
PA13.Signal=SYS_JTMS-SWDIO
PA14.Mode=Serial_Wire
PA14.Signal=SYS_JTCK-SWCLK
PA9.Mode=Asynchronous
PA9.Signal=USART1_TX
PB6.Mode=I2C
PB6.Signal=I2C1_SCL
PB7.Mode=I2C
PB7.Signal=I2C1_SDA
PD12.Signal=GPIO_Input
PD13.Signal=GPIO_Output
RCC.HSE_VALUE=25000000
RCC.SYSCLKFreq_VALUE=16000000
board=custom

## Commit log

2023-01-01 change directory from TA PCT100 to Tugas Akhir
2023-01-01 change voltage formula, GUI, timestamp
2023-01-01 adding data observation for open loop
2023-01-02 adding level transmitter regression
2023-01-02 changing desired tank level into 20cm, find m & c
2023-01-02 changing desired tank level into 20cm, substitute m & c
2023-01-02 [Worked] Koding closed loop Pak Hady Mas Khoiruz
2023-01-02 adding comment # for scaling vLTfeedback-->level & otherwise for controller output signal
2023-01-02 program fuzzy closed loop, but false membership function
2023-01-02 simplify equation
2023-01-02 test plot skfuzzy membership
2023-01-02 update closedLoop selasa pagi 5AM
2023-01-03 adding MQTT feature & its configuration
2023-01-03 hasil re-run rabu pagi 5AM
2023-01-03 using azzam membership function
2023-01-11 update condition timeNow-timeLast
2023-01-17 Change variable name and adding flow plot (right)
2023-01-17 add system identification file
2023-01-20 regresi FT data dr level
2023-01-20 open csv
2023-01-25 change datasets directory
2023-01-25 add multiple subscibe topics
2023-01-25 change FT transfer function from regression
2023-01-25 move csv datasets into a new directory
2023-01-26 configure inner loop, add SP transfer function from flow into level
2023-01-27 Solved to Subscribe Multiple Topics
2023-01-27 Add Subscribe Multiple Topics (MFoutput)
2023-01-27 Add comment QoS
2023-02-01 change Gain SP flow, output controller Outer level, from regresi_FT.py (hasil konsul P.Hady)
2023-02-01 add print(flow_sebenarnya) for getting SP inner gain from level loop
2023-02-01 Initial StepInfo
2023-02-01 Initial Commit ClosedLoop Bu Tri
2023-05-08 Initial commit MATLAB program
2023-05-08 add m_LT, c_LT for flow measurement
2023-05-09 able to approximate flow meter model in lt/min
2023-05-11 Multiple ADC STM can perform open loop for drain valve
2023-05-29 identify Ao valve (man & mov)
2023-06-02 MATLAB using direct NN being solved
2023-06-02 Pseudocode NN in c program
2023-07-20 adding testing description on README.md
2023-07-20 add regresi description on README.md
2023-07-25 Change Author TA in README.md
2023-11-25 add Datasets
2023-11-25 add Receipt
2023-11-25 add Buying Report.xlsx
2023-11-25 add Manual Book Embedded System Kit
2023-11-25 add Rafif level sensor data
2023-11-25 add Final Project reference
2023-11-25 rename folder to Thesis Reference
2023-11-25 add Sidang Proposal (dokumen dan slide ppt)
2023-11-25 move into Backup File folder (restructurize directory hierarcy)
2023-11-25 add Lecture Examiner Question on Thesis Defense
2023-11-25 add Faris's Weekly Undergrad Progress
2023-11-25 add Pedoman Penyusunan Buku TA ITS S1
2023-11-25 add Embedded System Kit Datasheet
2023-11-25 add Proposal Backup 10 Jan 2023
2023-11-25 update ppt bimbingan
2023-11-25 add burkert motor valve datasheet
2023-11-25 add Modelling sama untuk semua rekan PCT
2023-11-25 update ppt bimbingan 14 maret-20 april 2023
2023-11-25 add documentation (photo)
2023-11-25 update README.md with video documentation
2023-11-25 add Datasheet, Manual, and Installer
2023-11-25 add ADAM5000L/TCP Datasheet, Manual, and Installer
2023-11-25 add PPT Reno Fix
2023-11-25 add referensi ppt sempro
2023-11-25 add Rev0 and Rev1 backup Proposal TA Faris
2023-11-25 rename folder Slide PPT Proposal
2023-11-25 rename folder Proposal
2023-11-25 rename folder Konten Sidang dan Proposal TA
2023-11-25 add Lembar Pengesahan Proposal TA
2023-11-25 add skema diagram Buku TA Microsoft Visio
2023-11-25 rename MQTT to Rafif's MQTT App
2023-11-25 restructurize USB4716 folder
2023-11-25 add Theory Book
2023-11-25 rename folder References
2023-11-25 Restructurize References
2023-11-25 add Faris's Journal Reference
2023-11-25 move TA NN to Previous Thesis
2023-11-25 rename folder NN to Neural Network Journal
2023-11-25 update Readme.md with testing video implementation
2023-11-25 add Plant Modelling and Simulation
2023-11-25 add PCB Schematic for Implementation
2023-11-25 add System Identification Reference
2023-11-25 add PPT sidang TA Faris
2023-11-25 add Buku TA Faris
2023-11-25 add mathematical and physical modelling
2023-11-25 add prototype photo
2023-11-26 add 3D Acrylic Model and 3D Print USB-TTL
2023-11-26 add NN-SANARX Journal Reference
2023-11-26 add Proteus Simulation
2023-11-26 add Matlab testing
2023-11-26 change folder into Modelling and Testing using ADAM5000L TCP
2023-11-26 add dokumen TA from folder Draft TA
2023-11-26 add Tank Modelling
2023-11-26 add Previous Thesis
2023-11-26 update PPT Sidang TA
2023-11-26 add ADAM5000L python testing
2023-11-26 add NN journal
2023-11-26 Backup main.c with NN algorithm
2023-11-26 add Tank Mathematical Modelling Journal
2023-11-26 move into Khoirus & Rafif's folder: PCT100 with ADAM5000L
2023-11-26 move USB4716 python library
2023-11-26 move into Tank Modelling folder
2023-11-26 move into USB4716 folder
2023-11-26 move into Tank Level Modelling folder
2023-11-26 move into PCT100 with ADAM5000L folder
2023-11-26 move into STM32 folder
2023-11-26 move into ADAM4000L folder
2023-11-26 move respon DAC PWM
2023-11-26 move simulink RC filter to proteus folder
2023-11-26 move .vi into USB4716 folder
2023-11-26 move into ADAM5000L folder
2023-11-27 add TA Dedy Bambang about PID-GA Induction Motor
2023-11-27 add TA PCT100 Wisuda 128 dan 127
2023-11-28 update README.md with complete directory list
2024-04-26 add Form Ekivalensi
2024-04-26 add Excel Rekap SKS Matkul
2024-04-26 add PRBS Generator.m
2024-04-26 add Prototype Documentation
2024-04-26 add PCB Board Cache File

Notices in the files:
parts and their libraries:
diy-modules: Released under the Creative Commons Attribution 4.0 International License: http://creativecommons.org/licenses/by/4.0
ADUM1250: Released under the Creative Commons Attribution-ShareAlike 4.0 License
https://creativecommons.org/licenses/by-sa/4.0
